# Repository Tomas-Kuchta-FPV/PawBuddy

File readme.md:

# PawBuddy
> Status: PCB Designed, ordered. CAD need to be drawn up  
> This is my Graduation Project. YAY  
> **V1.2**  

It's aiming at making cheaper alternatives to classic GSM, GPS or propriatery radio dog trackers.  

## PCB Features
- RAK3640
- 3A charging
- indication LED's
- PCB art! Even in the schematic. ;)
- minimal footprint (25x51)
- mounting holes

## Manufacturing files

Gerber, drill, BOM, position, and netlist files are included in the versioned production archives under [`PCB/production/`](PCB/production/).  

Open the project in KiCad 9 or newer to inspect or modify the schematic and PCB. PDF exports and an interactive HTML BOM are also available in the production directory.  

## Bill of materials

The complete BOM is available as:

- [`BOM.ods`](BOM.ods) - all of the components for this prject
- [`PCB/production/bom.csv`](PCB/production/bom.csv) - just the PCB cmponents

## References
https://heltec.org/project/mesh-node-t114/  
https://docs.rakwireless.com/product-categories/wisduo/rak4630-module/datasheet/#schematic-diagram  
https://github.com/meshtastic/firmware/tree/develop/variants/nrf52840/rak4631

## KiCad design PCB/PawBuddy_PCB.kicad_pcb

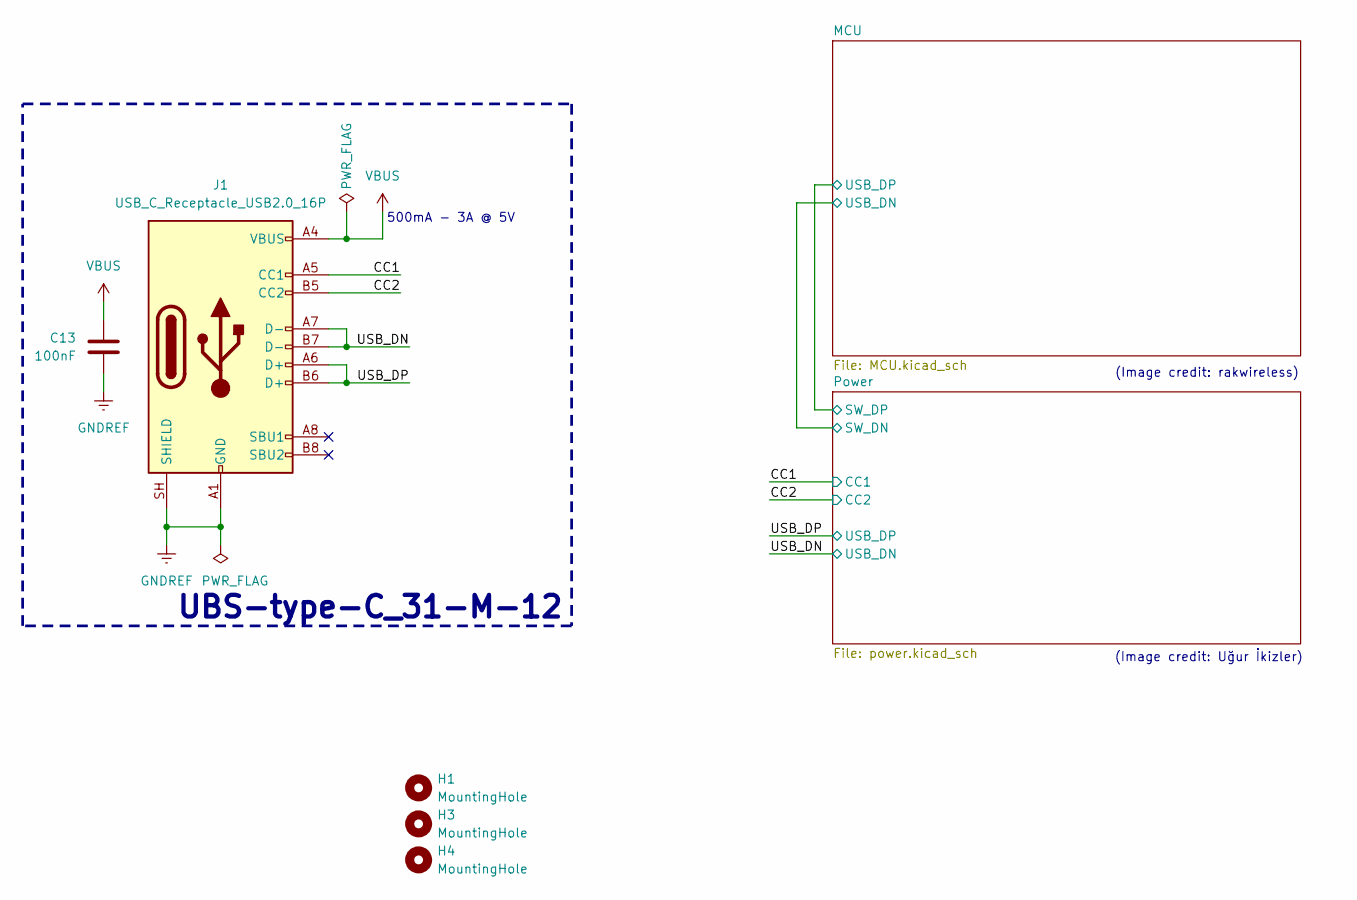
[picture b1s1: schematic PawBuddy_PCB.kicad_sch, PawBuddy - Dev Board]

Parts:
C13: 100nF; C_0603_1608Metric_Pad1.08x0.95mm_HandSolder; MPN C0603C104K3RACTU
H1, H3, H4: MountingHole; MountingHole_2.2mm_M2_DIN965
J1: USB_C_Receptacle_USB2.0_16P; USB_C_Receptacle_HRO_TYPE-C-31-M-12; MPN UJ20-C-H-G-SMT-2A-P16-TR

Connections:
/CC1: J1.A5 (CC1); also elsewhere on the board
/CC2: J1.B5 (CC2); also elsewhere on the board
/USB_DN: J1.A7 (D-), J1.B7 (D-); also elsewhere on the board
/USB_DP: J1.A6 (D+), J1.B6 (D+); also elsewhere on the board
GNDREF: C13.2, J1.A1 (GND), J1.A12 (GND), J1.B1 (GND), J1.B12 (GND), J1.SH (SHIELD); also elsewhere on the board
VBUS: C13.1, J1.A4 (VBUS), J1.A9 (VBUS), J1.B4 (VBUS), J1.B9 (VBUS); also elsewhere on the board

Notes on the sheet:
500mA - 3A @ 5V
(Image credit: rakwireless)
(Image credit: Uğur İkizler)
UBS-type-C_31-M-12

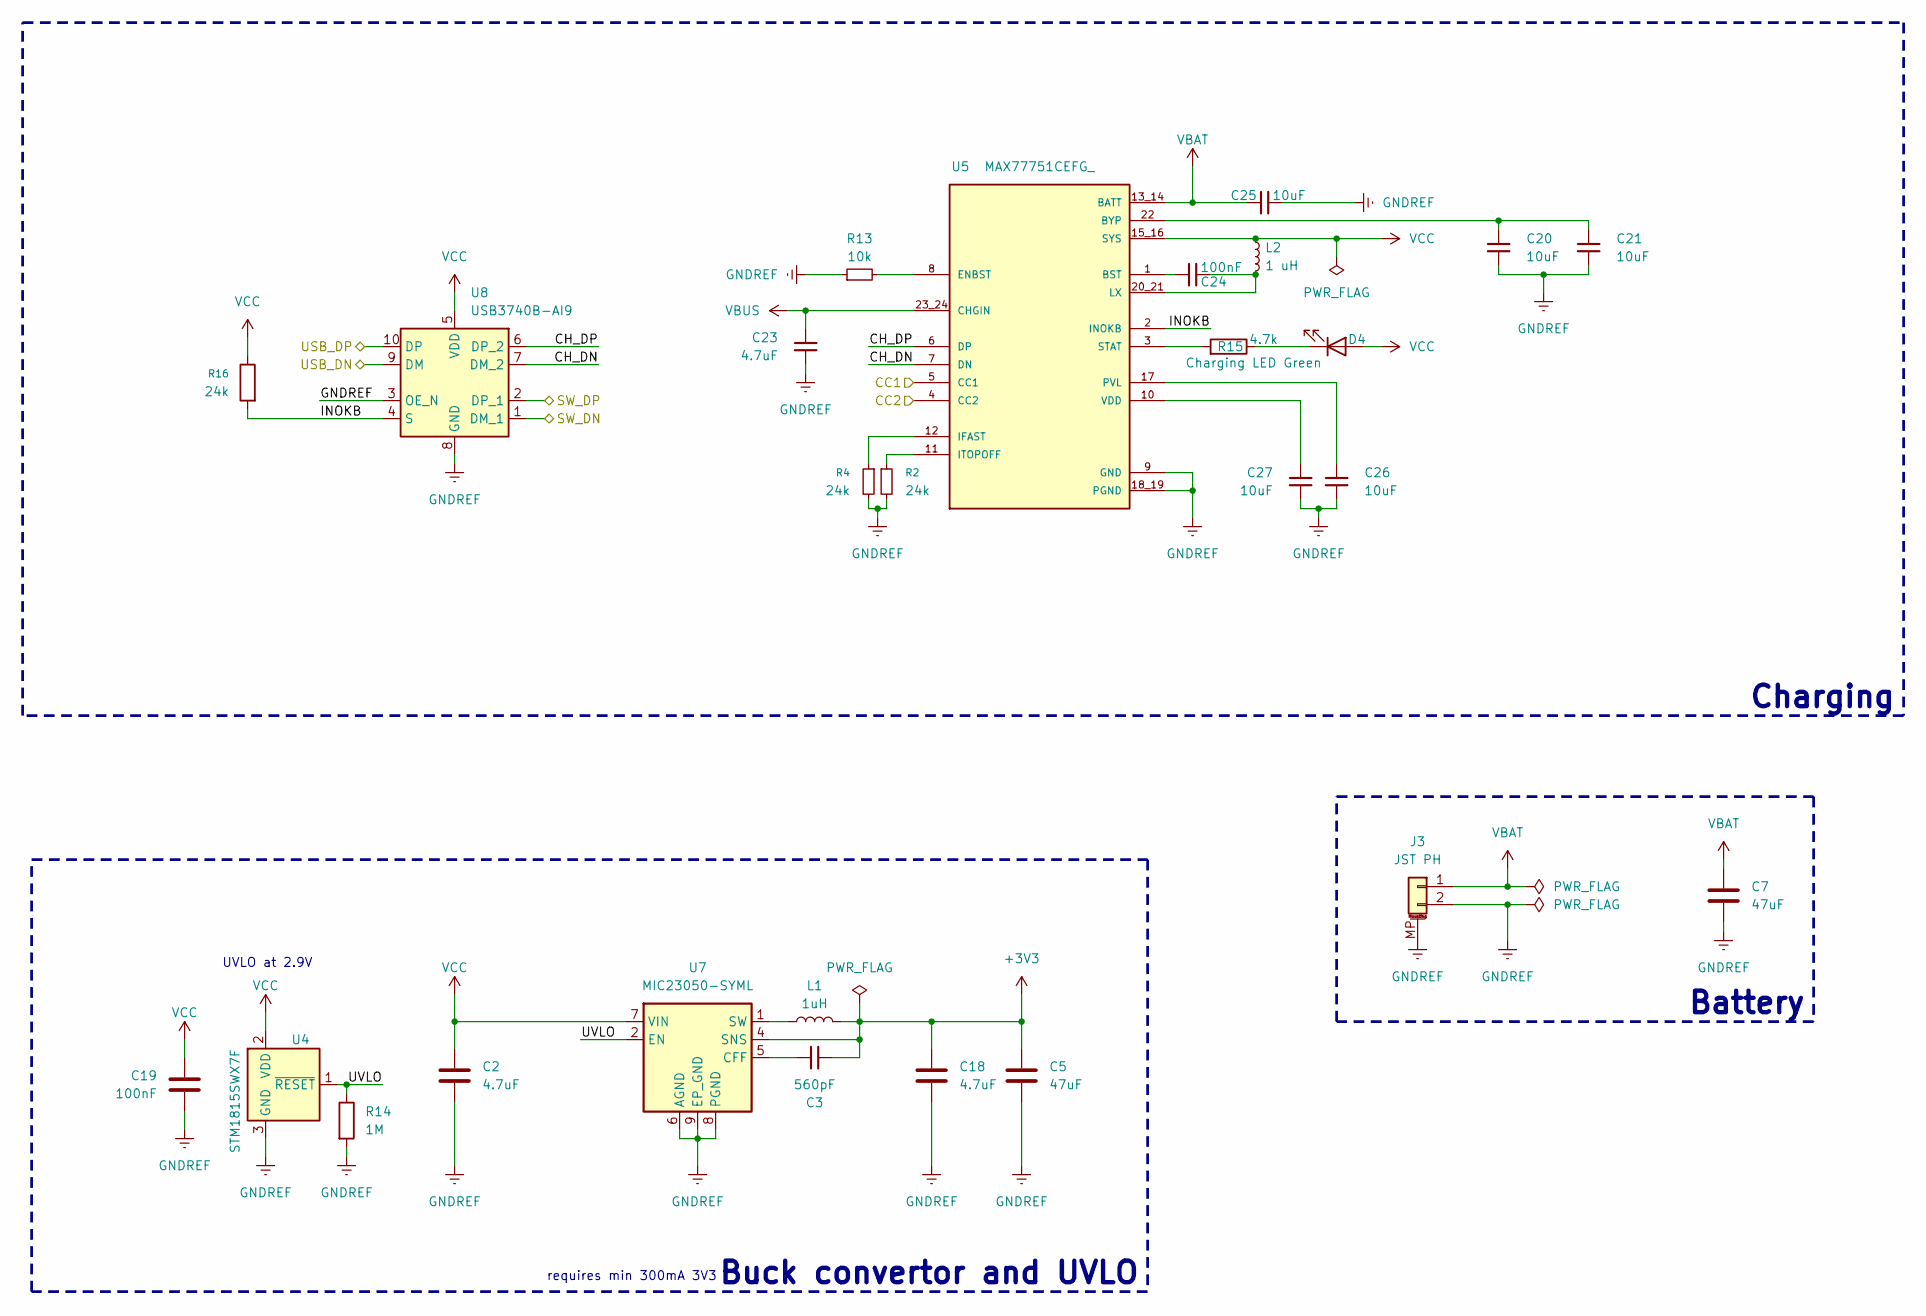
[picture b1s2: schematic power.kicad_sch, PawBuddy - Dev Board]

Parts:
C2, C18, C23: 4.7uF; C_0603_1608Metric_Pad1.08x0.95mm_HandSolder; MPN C0603C475K8PACTU
C3: 560pF; C_0603_1608Metric_Pad1.08x0.95mm_HandSolder; MPN C0603C561J5GACTU
C5, C7: 47uF; C_0805_2012Metric_Pad1.18x1.45mm_HandSolder; MPN CL21A476MQYNNNE
C19, C24: 100nF; C_0603_1608Metric_Pad1.08x0.95mm_HandSolder; MPN C0603C104K3RACTU
C20, C21, C25, C26, C27: 10uF; C_0603_1608Metric_Pad1.08x0.95mm_HandSolder; MPN ZRB18AR61E106ME01L
D4: Charging LED Green; LED_0603_1608Metric_Pad1.05x0.95mm_HandSolder; MPN 150060GS75000
J3: JST PH; JST_PH_S2B-PH-SM4-TB_1x02-1MP_P2.00mm_Horizontal; MPN S2B-PH-SM4-TB(LF)(SN)
L1: 1uH; L_0805_2012Metric_Pad1.05x1.20mm_HandSolder; MPN AOTA-B201608S1R0MT
L2: 1 uH; L_0805_2012Metric_Pad1.05x1.20mm_HandSolder; MPN AOTA-B201608S1R0MT
R2, R4, R16: 24k; R_0603_1608Metric_Pad0.98x0.95mm_HandSolder; MPN ERJUP3J243V
R13: 10k; R_0603_1608Metric_Pad0.98x0.95mm_HandSolder; MPN RC0603JR-0710KL
R14: 1M; R_0603_1608Metric_Pad0.98x0.95mm_HandSolder; MPN RC0603FR-071ML
R15: 4.7k; R_0603_1608Metric_Pad0.98x0.95mm_HandSolder; MPN RE0603DRE074K7L
U4: STM1815SWX7F; SOT-23-3
U5: MAX77751CEFG_; IC_MAX77751CEFG; MPN MAX77751CEFG+
U7: MIC23050-SYML; Micrel_MLF-8-1EP_2x2mm_P0.5mm_EP0.6x1.2mm_ThermalVias; MPN MIC23050-SYML-TR
U8: USB3740B-AI9; UQFN-10_1.6x2.1mm_P0.5mm; MPN USB3740B-AI9-TR

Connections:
+3V3: C3.1, C5.1, C18.1, L1.2, U7.4 (SNS); also elsewhere on the board
/CC1: U5.5 (CC1); also elsewhere on the board
/CC2: U5.4 (CC2); also elsewhere on the board
/MCU/USB_DN: U8.1 (DM_1); also elsewhere on the board
/MCU/USB_DP: U8.2 (DP_1); also elsewhere on the board
/Power/CH_DN: U5.7 (DN), U8.7 (DM_2)
/Power/CH_DP: U5.6 (DP), U8.6 (DP_2)
/Power/INOKB: R16.2, U5.2 (INOKB), U8.4 (S)
/Power/UVLO: R14.1, U4.1 (~RESET), U7.2 (EN)
/USB_DN: U8.9 (DM); also elsewhere on the board
/USB_DP: U8.10 (DP); also elsewhere on the board
GNDREF: C2.2, C5.2, C7.2, C18.2, C19.2, C20.2, C21.2, C23.2, C25.2, C26.2, C27.2, J3.2, J3.MP (MountPin), R2.2, R4.2, R13.1, R14.2, U4.3 (GND), U5.9 (GND), U5.18_19 (PGND), U7.6 (AGND), U7.8 (PGND), U7.9 (EP_GND), U8.3 (OE_N), U8.8 (GND); also elsewhere on the board
unnamed: D4.1 (K), R15.1
unnamed: C24.1, U5.1 (BST)
unnamed: C20.1, C21.1, U5.22 (BYP)
unnamed: R13.2, U5.8 (ENBST)
unnamed: R4.1, U5.12 (IFAST)
unnamed: R2.1, U5.11 (ITOPOFF)
unnamed: C24.2, L2.2, U5.20_21 (LX)
unnamed: C26.1, U5.17 (PVL)
unnamed: R15.2, U5.3 (STAT)
unnamed: C27.1, U5.10 (VDD)
unnamed: C3.2, U7.5 (CFF)
unnamed: L1.1, U7.1 (SW)
VBAT: C7.1, C25.1, J3.1, U5.13_14 (BATT); also elsewhere on the board
VBUS: C23.1, U5.23_24 (CHGIN); also elsewhere on the board
VCC: C2.1, C19.1, D4.2 (A), L2.1, R16.1, U4.2 (VDD), U5.15_16 (SYS), U7.7 (VIN), U8.5 (VDD)

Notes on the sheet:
requires min 300mA 3V3
UVLO at 2.9V
Charging
Buck convertor and UVLO
Battery

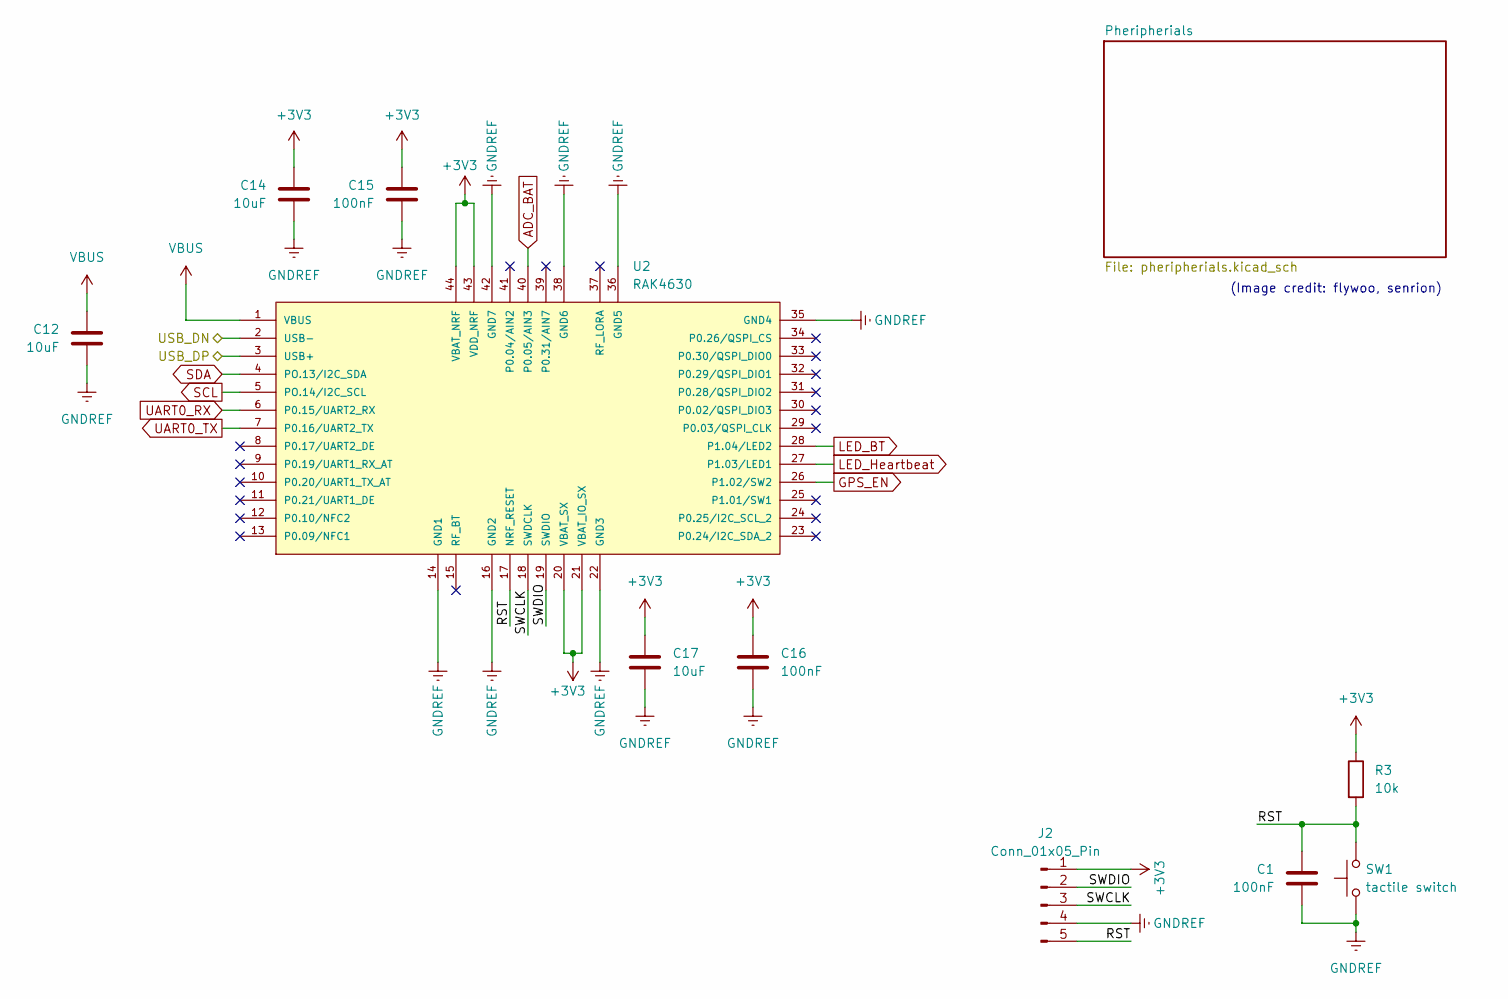
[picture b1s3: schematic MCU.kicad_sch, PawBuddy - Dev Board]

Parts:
C1, C15, C16: 100nF; C_0603_1608Metric_Pad1.08x0.95mm_HandSolder; MPN C0603C104K3RACTU
C12, C14, C17: 10uF; C_0603_1608Metric_Pad1.08x0.95mm_HandSolder; MPN ZRB18AR61E106ME01L
J2: Conn_01x05_Pin; PinHeader_1x05_P1.27mm_Vertical; MPN N/A
R3: 10k; R_0603_1608Metric_Pad0.98x0.95mm_HandSolder; MPN RC0603JR-0710KL
SW1: tactile switch; SW_SPST_B3U-1000P; MPN B3U-1000P
U2: RAK4630; MPN RAK4630

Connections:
+3V3: C14.1, C15.1, C16.1, C17.1, J2.1, R3.1, U2.20 (VBAT_SX), U2.21 (VBAT_IO_SX), U2.43 (VDD_NRF), U2.44 (VBAT_NRF); also elsewhere on the board
/MCU/RST: C1.1, J2.5, R3.2, SW1.2, U2.17 (NRF_RESET)
/MCU/SWCLK: J2.3, U2.18 (SWDCLK)
/MCU/SWDIO: J2.2, U2.19 (SWDIO)
/MCU/USB_DN: U2.2 (USB-); also elsewhere on the board
/MCU/USB_DP: U2.3 (USB+); also elsewhere on the board
ADC_BAT: U2.40 (P0.05/AIN3); also elsewhere on the board
GNDREF: C1.2, C12.2, C14.2, C15.2, C16.2, C17.2, J2.4, SW1.1, U2.14 (GND1), U2.16 (GND2), U2.22 (GND3), U2.35 (GND4), U2.36 (GND5), U2.38 (GND6), U2.42 (GND7); also elsewhere on the board
GPS_EN: U2.26 (P1.02/SW2); also elsewhere on the board
LED_BT: U2.28 (P1.04/LED2); also elsewhere on the board
LED_Heartbeat: U2.27 (P1.03/LED1); also elsewhere on the board
SCL: U2.5 (PO.14/I2C_SCL); also elsewhere on the board
SDA: U2.4 (PO.13/I2C_SDA); also elsewhere on the board
UART0_RX: U2.6 (P0.15/UART2_RX); also elsewhere on the board
UART0_TX: U2.7 (P0.16/UART2_TX); also elsewhere on the board
VBUS: C12.1, U2.1 (VBUS); also elsewhere on the board

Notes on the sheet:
(Image credit: flywoo, senrion)

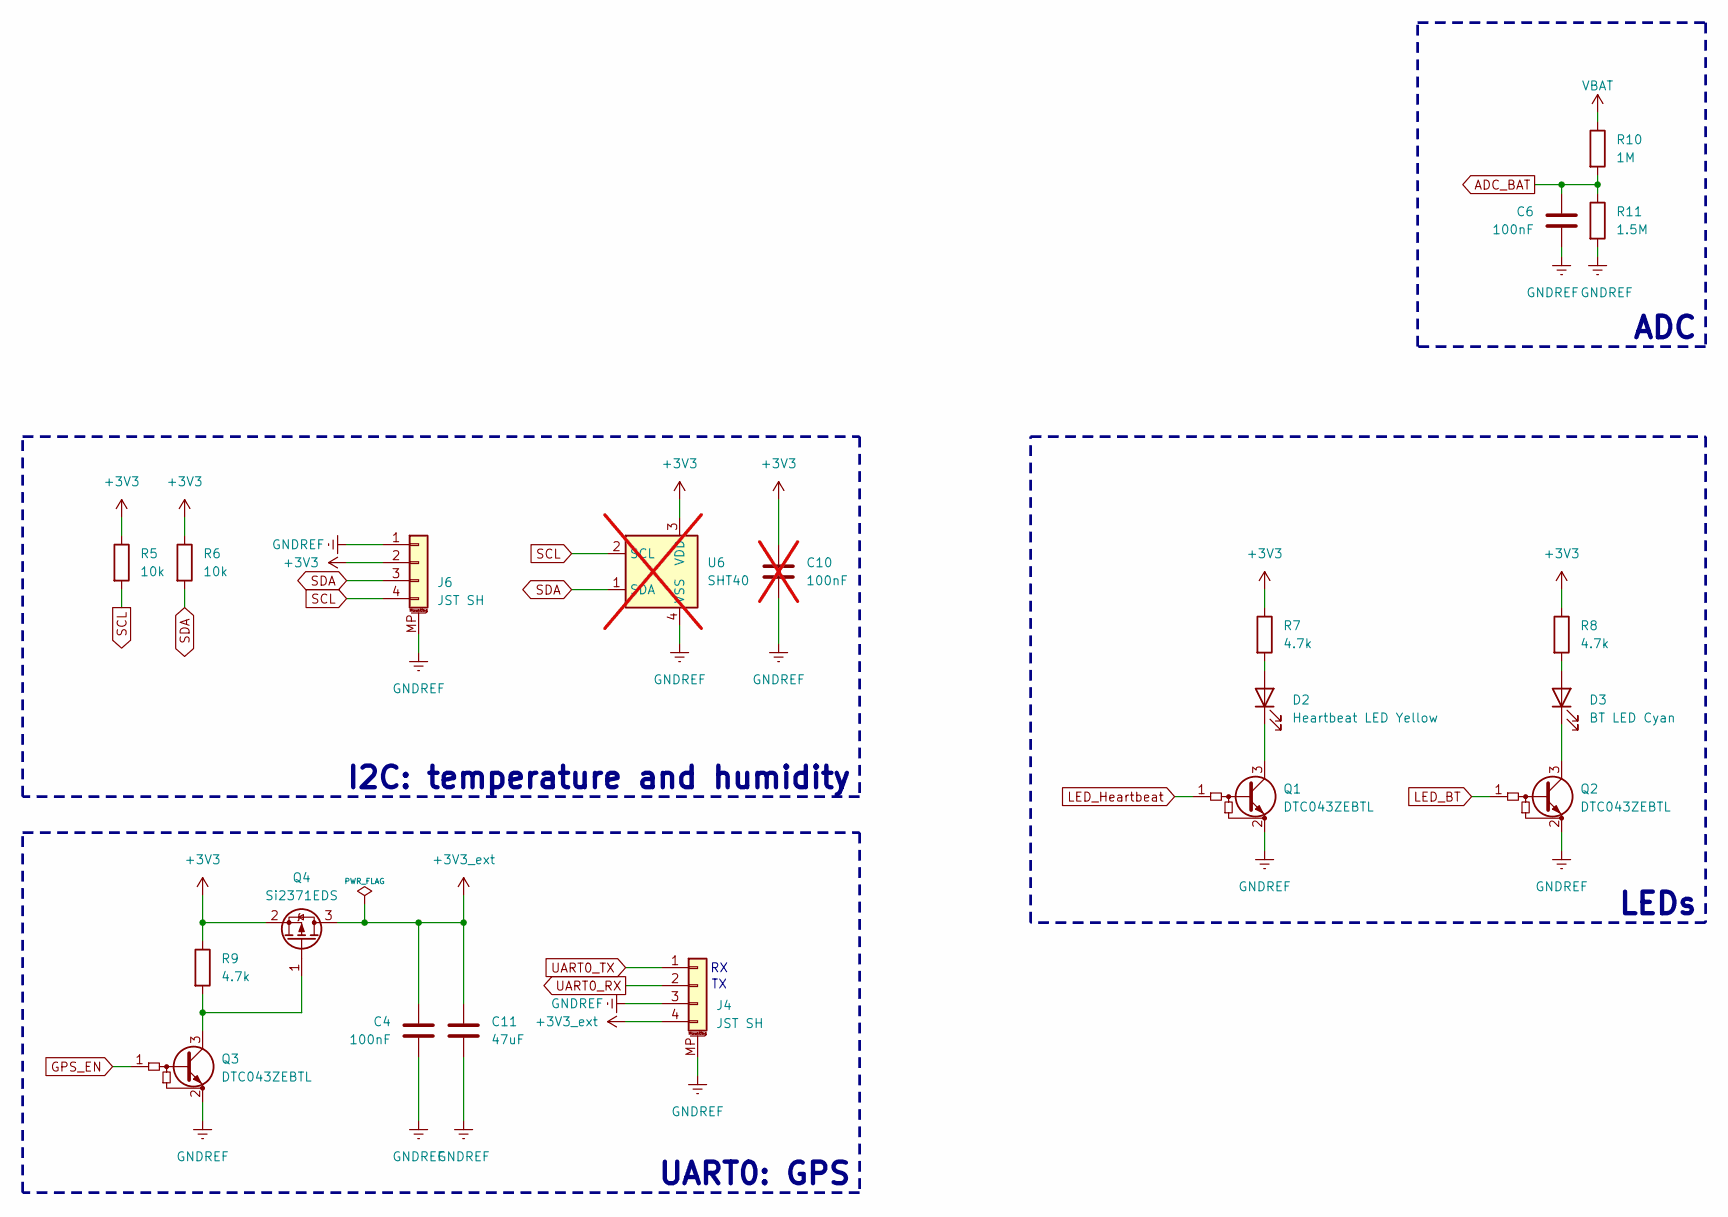
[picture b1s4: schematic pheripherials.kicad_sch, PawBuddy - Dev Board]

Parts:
C4, C6: 100nF; C_0603_1608Metric_Pad1.08x0.95mm_HandSolder; MPN C0603C104K3RACTU
C10: 100nF; C_0603_1608Metric_Pad1.08x0.95mm_HandSolder; MPN C0603C104K3RACTU; not fitted
C11: 47uF; C_0805_2012Metric_Pad1.18x1.45mm_HandSolder; MPN CL21A476MQYNNNE
D2: Heartbeat LED Yellow; LED_0603_1608Metric_Pad1.05x0.95mm_HandSolder; MPN 150060YS75000
D3: BT LED Cyan; LED_0603_1608Metric_Pad1.05x0.95mm_HandSolder; MPN 150060BS75000
J4, J6: JST SH; JST_SH_SM04B-SRSS-TB_1x04-1MP_P1.00mm_Horizontal; MPN SM04B-SRSS-TB(LF)(SN)
Q1, Q2, Q3: DTC043ZEBTL; SOT-416; MPN DTC043ZEBTL
Q4: Si2371EDS; SOT-23; MPN SI2371EDS-T1-GE3
R5, R6: 10k; R_0603_1608Metric_Pad0.98x0.95mm_HandSolder; MPN RC0603JR-0710KL
R7, R8, R9: 4.7k; R_0603_1608Metric_Pad0.98x0.95mm_HandSolder; MPN RE0603DRE074K7L
R10: 1M; R_0603_1608Metric_Pad0.98x0.95mm_HandSolder; MPN RC0603FR-071ML
R11: 1.5M; R_0603_1608Metric_Pad0.98x0.95mm_HandSolder; MPN MCWR06W1504FTL
U6: SHT40; Sensirion_DFN-4_1.5x1.5mm_P0.8mm_SHT4x_NoCentralPad; MPN SHT40-AD1B-R2; not fitted

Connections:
+3V3: C10.1, J6.2, Q4.2 (S), R5.1, R6.1, R7.1, R8.1, R9.1, U6.3 (VDD); also elsewhere on the board
+3V3_ext: C4.1, C11.1, J4.4, Q4.3 (D)
ADC_BAT: C6.1, R10.2, R11.1; also elsewhere on the board
GNDREF: C4.2, C6.2, C10.2, C11.2, J4.3, J4.MP (MountPin), J6.1, J6.MP (MountPin), Q1.2 (E), Q2.2 (E), Q3.2 (E), R11.2, U6.4 (VSS); also elsewhere on the board
GPS_EN: Q3.1 (B); also elsewhere on the board
LED_BT: Q2.1 (B); also elsewhere on the board
LED_Heartbeat: Q1.1 (B); also elsewhere on the board
unnamed: D2.2 (A), R7.2
unnamed: D2.1 (K), Q1.3 (C)
unnamed: D3.2 (A), R8.2
unnamed: D3.1 (K), Q2.3 (C)
unnamed: Q3.3 (C), Q4.1 (G), R9.2
SCL: J6.4, R5.2, U6.2 (SCL); also elsewhere on the board
SDA: J6.3, R6.2, U6.1 (SDA); also elsewhere on the board
UART0_RX: J4.2; also elsewhere on the board
UART0_TX: J4.1; also elsewhere on the board
VBAT: R10.1; also elsewhere on the board

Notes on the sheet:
LEDs
ADC
I2C: temperature and humidity
UART0: GPS

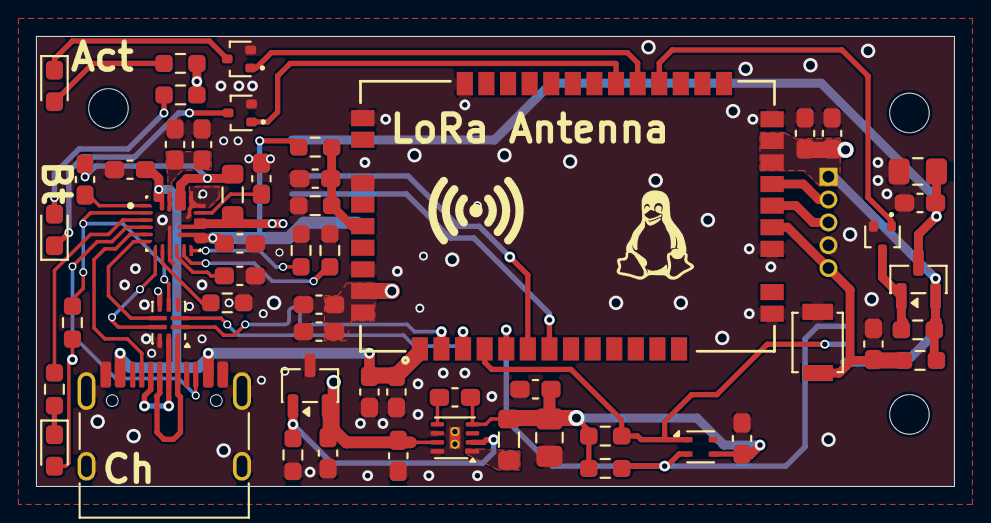
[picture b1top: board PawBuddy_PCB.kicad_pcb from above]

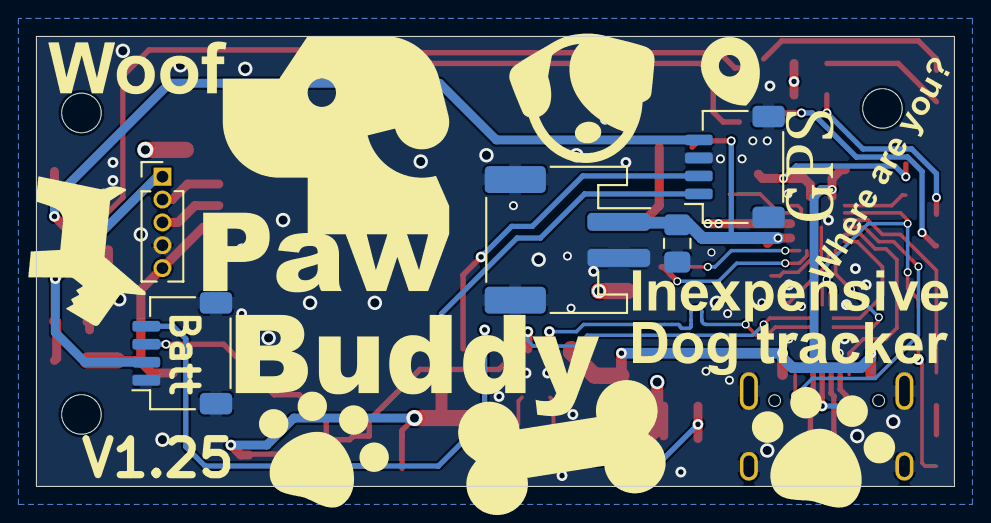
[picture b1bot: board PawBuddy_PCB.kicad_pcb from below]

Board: 4 copper layers, 51.0 x 25.0 mm, 62 parts (5 on the bottom side), 44 nets.

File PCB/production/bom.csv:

Designator,Footprint,Quantity,Value,LCSC Part #
"C1, C13, C15, C16, C19, C24, C4, C6",0603,8,100nF,C0603C104K3RACTU
"C11, C5, C7",0805,3,47uF,CL21A476MQYNNNE
"C12, C14, C17, C20, C21, C25, C26, C27",0603,8,10uF,ZRB18AR61E106ME01L
"C18, C2, C23",0603,3,4.7uF,C0603C475K8PACTU
C3,0603,1,560pF,C0603C561J5GACTU
D2,0603,1,Heartbeat LED Yellow,150060YS75000
D3,0603,1,BT LED Cyan,150060BS75000 
D4,0603,1,Charging LED Green,150060GS75000
J1,USB_C_Receptacle_HRO_TYPE-C-31-M-12,1,USB_C_Receptacle_USB2.0_16P,UJ20-C-H-G-SMT-2A-P16-TR
J3,JST_PH_S2B-PH-SM4-TB_1x02-1MP_P2.00mm_Horizontal,1,JST PH,S2B-PH-SM4-TB(LF)(SN)
"J4, J6",JST_SH_SM04B-SRSS-TB_1x04-1MP_P1.00mm_Horizontal,2,JST SH,SM04B-SRSS-TB(LF)(SN) 
L1,0805,1,1uH,AOTA-B201608S1R0MT
L2,0805,1,1 uH,AOTA-B201608S1R0MT
"Q1, Q2, Q3",SOT-416,3,DTC043ZEBTL,DTC043ZEBTL
Q4,SOT-23,1,Si2371EDS,SI2371EDS-T1-GE3
"R10, R14",0603,2,1M,RC0603FR-071ML
R11,0603,1,1.5M,MCWR06W1504FTL
"R13, R3, R5, R6",0603,4,10k,RC0603JR-0710KL
"R15, R7, R8, R9",0603,4,4.7k,RE0603DRE074K7L
"R16, R2, R4",0603,3,24k,ERJUP3J243V
SW1,SW_SPST_B3U-1000P,1,tactile switch,B3U-1000P
U2,RAK4630,1,RAK4630,RAK4630
U4,SOT-23-3,1,STM1815SWX7F,-
U5,IC_MAX77751CEFG,1,MAX77751CEFG_,MAX77751CEFG+
U7,Micrel_MLF-8-1EP_2x2mm_P0.5mm_EP0.6x1.2mm_ThermalVias,1,MIC23050-SYML,MIC23050-SYML-TR
U8,UQFN-10_1.6x2.1mm_P0.5mm,1,USB3740B-AI9,USB3740B-AI9-TR
